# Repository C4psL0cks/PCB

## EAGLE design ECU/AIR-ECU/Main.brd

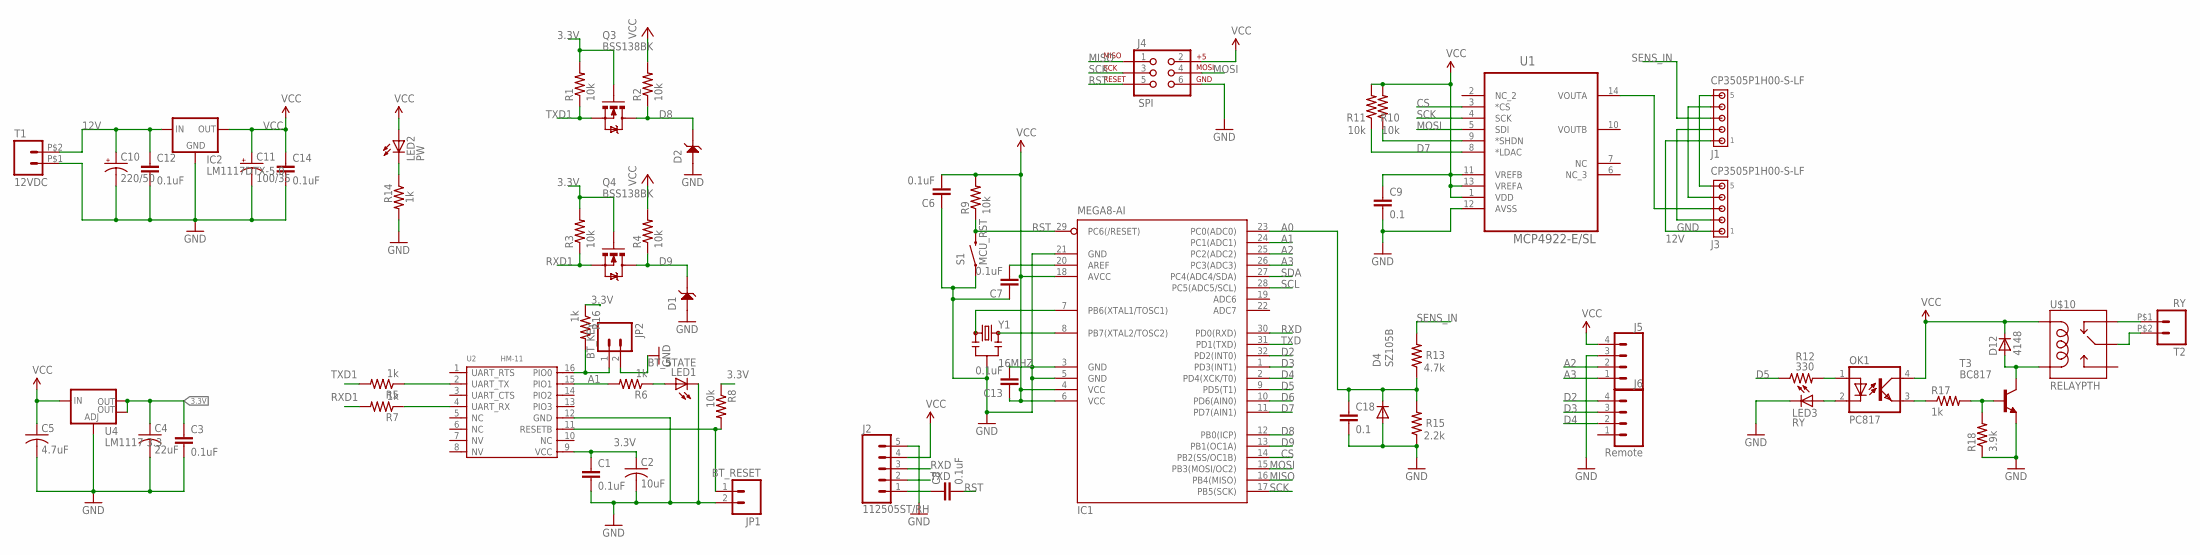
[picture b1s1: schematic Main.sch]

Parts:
C1, C3, C6, C7, C8, C12, C13, C14: 0.1uF; 0805
C2: 10uF; C1206
C4: 22uF; C1206
C5: 4.7uF; C1206
C9, C18: 0.1; 0805
C10: 220/50; 153CLV-1010
C11: 100/35; 153CLV-0605
D1, D2: SMF5.0A; SOD123-2.7X1.6
D4: SZ105B; DO-214AC
D12: 4148; SOD80
IC1: MEGA8-AI; TQFP32-08
IC2: LM1117DTX-5.0; TO252
J1, J3: CP3505P1H00-S-LF; 1445055-5
J2: 112505ST/RH; JST-5-PTH
J4: SPI; 2X3
J5: CONN_04JST-PTH; JST-4-PTH
J6: Remote; JST-4-PTH
JP1: BT_RESET; 1X02
JP2: BT_KEY; 1X02
LED1: BT_STATE; LED3MM
LED2: PW; LED3MM
LED3: RY; LED3MM
OK1: PC817; DIL4-SMD
Q3, Q4: BSS138BK; SOT23-3
R1, R2, R3, R4, R8, R9, R10, R11: 10k; 0805
R5, R6, R7, R14, R16, R17: 1k; 0805
R12: 330; 0805
R13: 4.7k; 0805
R15: 2.2k; 0805
R18: 3.9k; 0805
S1: MCU_RST; TACTILE-SWITCH-1101NE
T1: 12VDC; ED350V-02P
T2: RY; ED350V-02P
T3: BC817; SOT23-BEC
U1: MCP4922-E/SL; SOIC127P600X175-14N
U2: HM-11; 16P-18.5X13.5X0.8
U4: LM1117 3.3; SOT223
U$10: RELAYPTH; SRD-05VDC-SL-C
Y1: 16MHZ; RESONATOR-SMD

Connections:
3.3V: C1.1, C2.1, C3.1, C4.1, Q3.1 (G), Q4.1 (G), R1.2, R3.2, R8.1, R16.1, U2.9 (VCC), U4.2 (OUT), U4.4 (OUT)
12V: C10.+, C12.1, IC2.2 (IN), J1.1, J3.1, T1.P$2 (2)
A0: C18.1, D4.C, IC1.23 (PC0(ADC0)), R13.1, R15.2
A1: IC1.24 (PC1(ADC1)), R6.2, U2.15 (PIO1)
A2: IC1.25 (PC2(ADC2)), J5.2
A3: IC1.26 (PC3(ADC3)), J5.1
CS: IC1.14 (PB2(SS/OC1B)), U1.3 (*CS)
D2: IC1.32 (PD2(INT0)), J6.4
D3: IC1.1 (PD3(INT1)), J6.3
D4: IC1.2 (PD4(XCK/T0)), J6.2
D5: IC1.9 (PD5(T1)), R12.1
D6: IC1.10 (PD6(AIN0))
D7: IC1.11 (PD7(AIN1)), R11.1, U1.8 (*LDAC)
D8: D2.2, IC1.12 (PB0(ICP)), Q3.3 (D), R2.1
D9: D1.2, IC1.13 (PB1(OC1A)), Q4.3 (D), R4.1
GND: C1.2, C2.2, C3.2, C4.2, C5.2, C6.1, C7.1, C9.2, C10.-, C11.-, C12.2, C13.2, C14.2, C18.2, D1.1, D2.1, D4.A, IC1.3 (GND), IC1.5 (GND), IC1.21 (GND), IC2.1 (GND), J1.2, J2.5, J3.2, J4.6, J5.3, JP1.2, JP2.2, LED1.K (C), LED3.K (C), R14.2, R15.1, R18.1, S1.1, T1.P$1 (1), T3.E, U1.12 (AVSS), U2.12 (GND), U4.1 (ADJ), Y1.2
MISO: IC1.16 (PB4(MISO)), J4.1
MOSI: IC1.15 (PB3(MOSI/OC2)), J4.4, U1.5 (SDI)
unnamed: LED1.A, R6.1
unnamed: JP2.1, R16.2, U2.16 (PIO0)
unnamed: R5.1, U2.2 (UART_TX)
unnamed: JP1.1, R8.2, U2.11 (RESETB)
unnamed: IC1.8 (PB7(XTAL2/TOSC2)), Y1.3
unnamed: R7.1, U2.4 (UART_RX)
unnamed: IC1.7 (PB6(XTAL1/TOSC1)), Y1.1
unnamed: C7.2, IC1.20 (AREF)
unnamed: C8.1, J2.1
unnamed: LED2.K (C), R14.1
unnamed: J3.3, U1.14 (VOUTA)
unnamed: J1.5, J3.5
unnamed: J1.4, J3.4
unnamed: R10.1, U1.9 (*SHDN)
unnamed: OK1.3 (EMIT), R17.1
unnamed: R17.2, R18.2, T3.B
unnamed: D12.2 (A), T3.C, U$10.COIL0
unnamed: OK1.1 (A), R12.2
unnamed: T2.P$1 (1), U$10.SWCLOSED (SWCLOSE)
unnamed: T2.P$2 (2), U$10.SWCOMMON
unnamed: LED3.A, OK1.2 (C)
RST: C8.2, IC1.29 (PC6(/RESET)), J4.5, R9.1, S1.2
RXD: IC1.30 (PD0(RXD)), J2.3
RXD1: Q4.2 (S), R3.1, R7.2
SCK: IC1.17 (PB5(SCK)), J4.3, U1.4 (SCK)
SCL: IC1.28 (PC5(ADC5/SCL))
SDA: IC1.27 (PC4(ADC4/SDA))
SENS_IN: J1.3, R13.2
TXD: IC1.31 (PD1(TXD)), J2.2
TXD1: Q3.2 (S), R1.1, R5.2
VCC: C5.1, C6.2, C9.1, C11.+, C13.1, C14.1, D12.1 (C), IC1.4 (VCC), IC1.6 (VCC), IC1.18 (AVCC), IC2.TAB (OUT), J2.4, J4.2, J5.4, LED2.A, OK1.4 (COL), R2.2, R4.2, R9.2, R10.2, R11.2, U1.1 (VDD), U1.11 (VREFB), U1.13 (VREFA), U4.3 (IN), U$10.COIL1

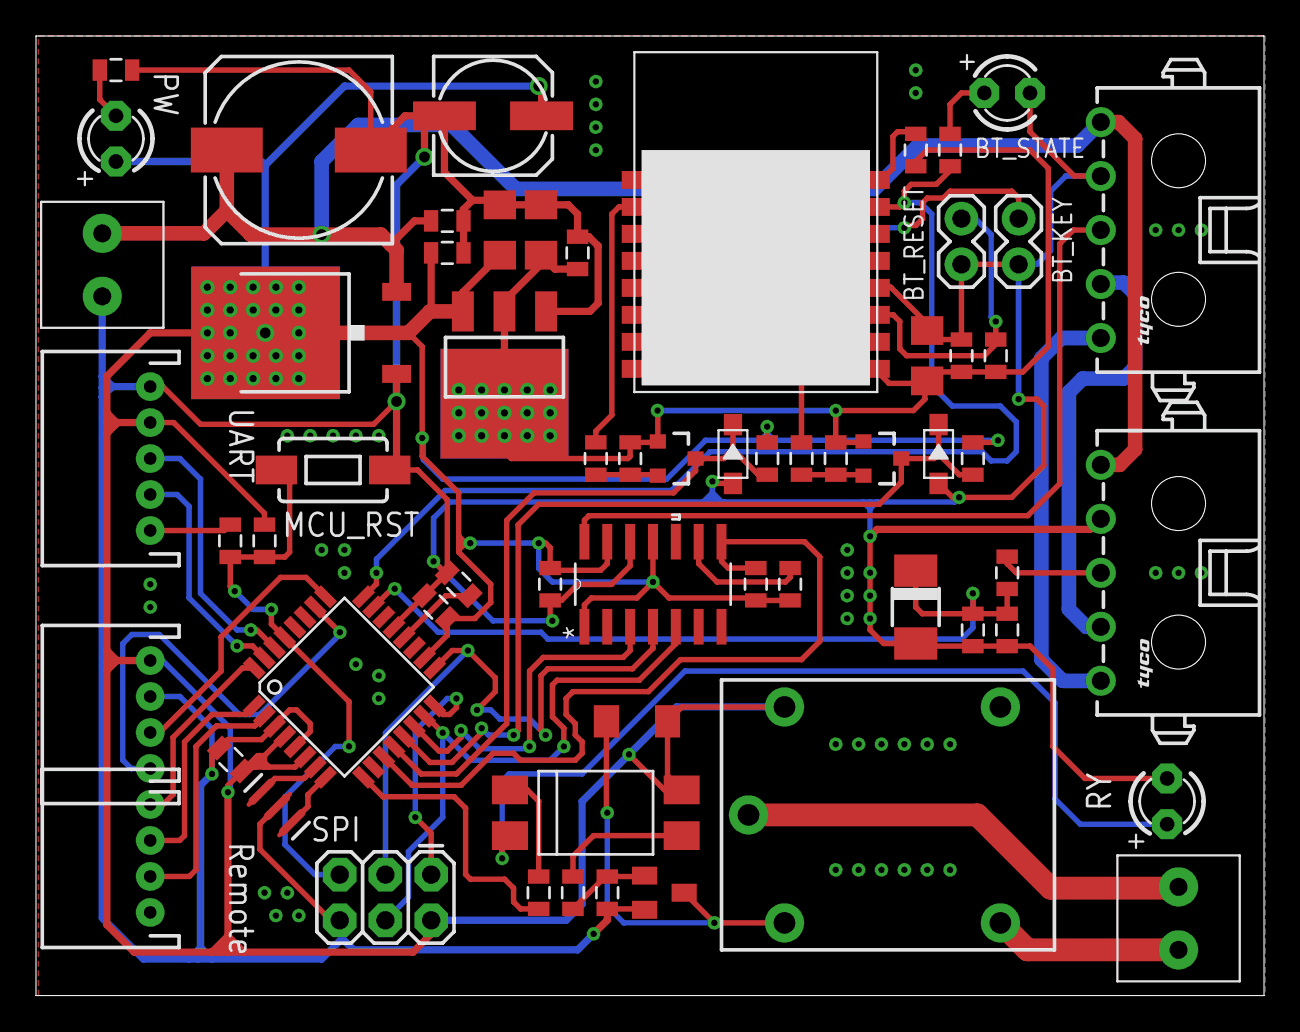
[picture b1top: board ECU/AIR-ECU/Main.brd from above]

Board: 2 copper layers, 68.2 x 53.3 mm, 62 parts (0 on the bottom side), 46 nets.

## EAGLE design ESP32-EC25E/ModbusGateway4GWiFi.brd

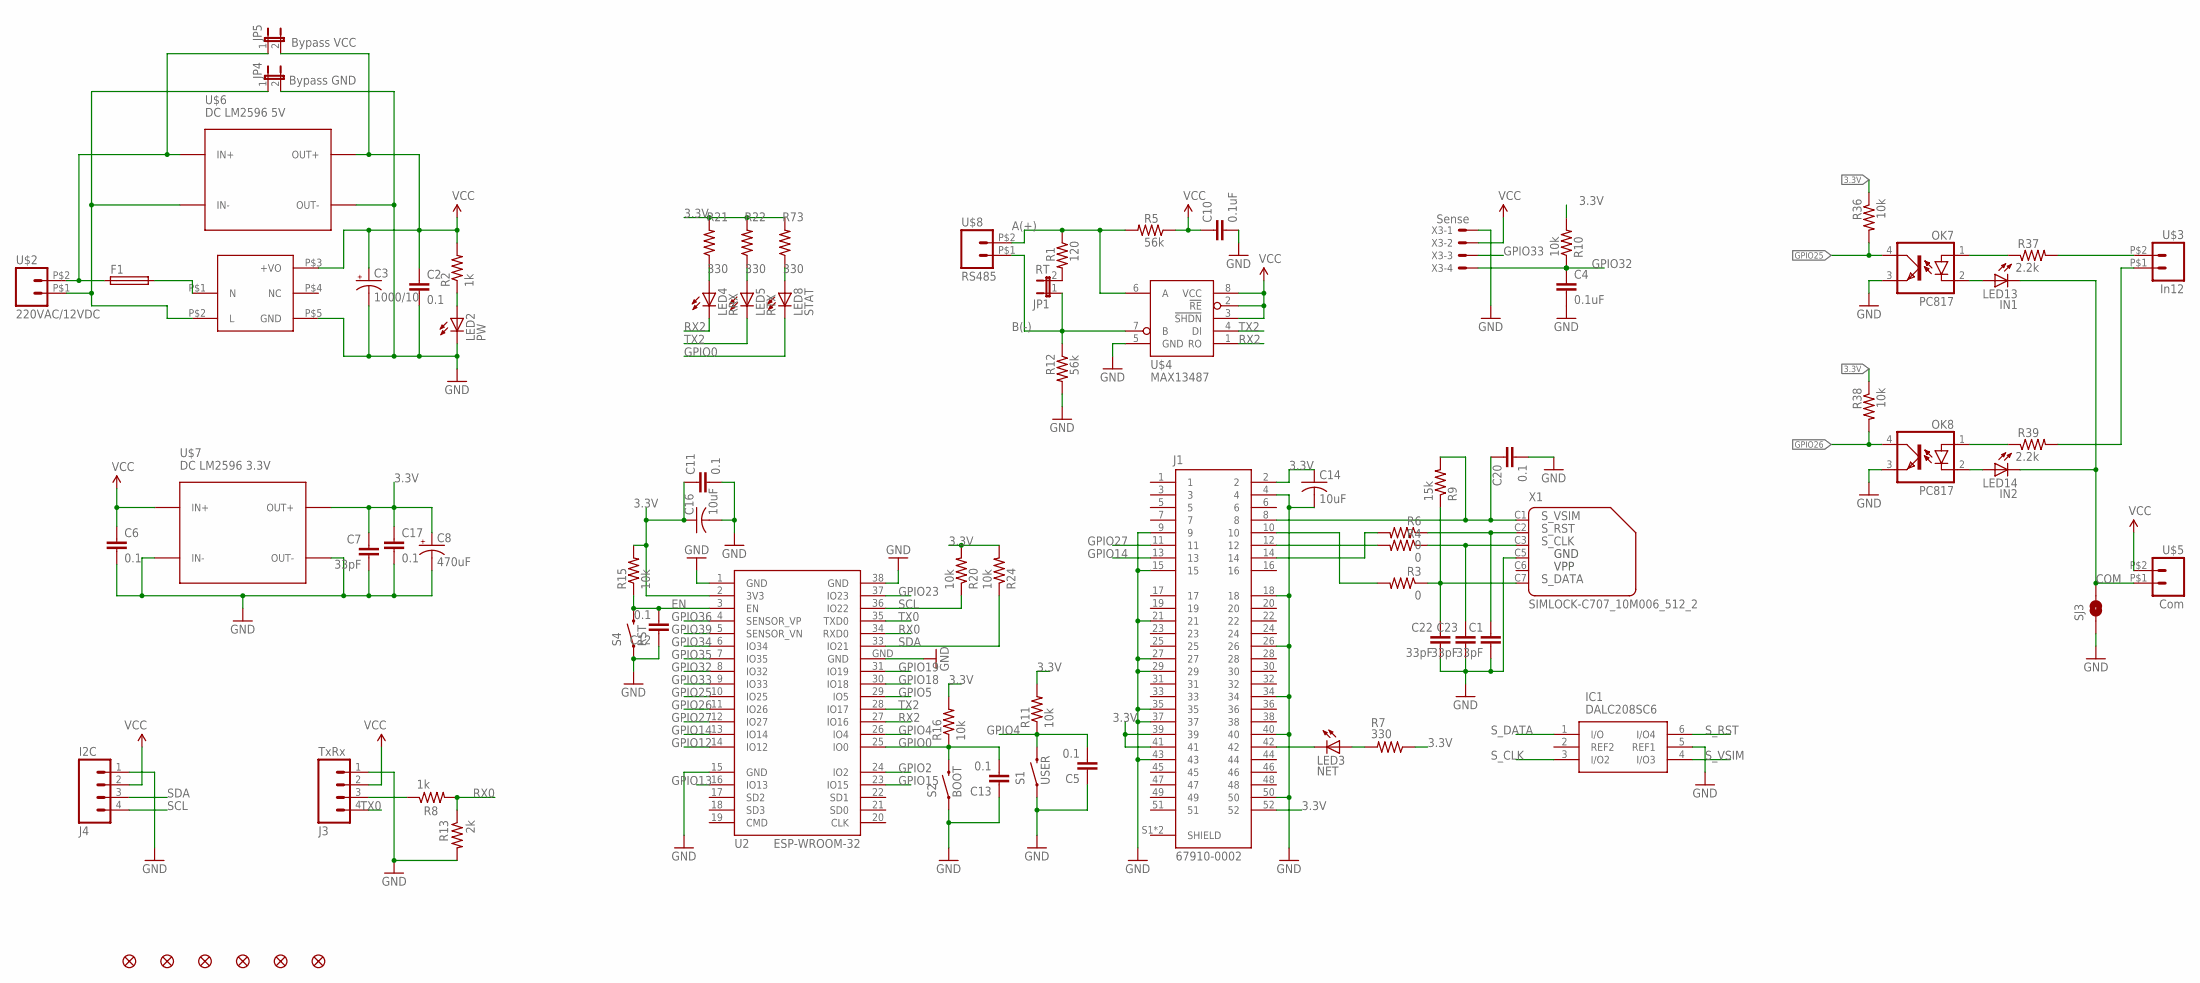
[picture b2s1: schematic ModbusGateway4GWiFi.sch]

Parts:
C1, C7, C22, C23: 33pF; 0805
C2, C5, C6, C11, C12, C13, C17, C20: 0.1; 0805
C3: 1000/10; 140CLH-1010
C4, C10: 0.1uF; 0805
C8: 470uF; 175TMP-0810
C14, C16: 10uF; C1206
F1: SH22,5A
IC1: DALC208SC6; SOT95P280X145-6N
J1: 67910-0002; MOLEX_67910-0002
J3: TxRx; MOLEX-1X4
J4: I2C; MOLEX-1X4
JP1: RT; 1X02
JP4: Bypass GND; SJ_2S-NO
JP5: Bypass VCC; SJ_2S-NO
JP8, JP9, JP10, JP11, JP12, JP16: FIDUCIAL1X2; FIDUCIAL-1X2
LED2: PW; CHIP-LED0805
LED3: NET; CHIP-LED0805
LED4: RRX; CHIP-LED0805
LED5: RTX; CHIP-LED0805
LED8: STAT; CHIP-LED0805
LED13: IN1; CHIP-LED0805
LED14: IN2; CHIP-LED0805
OK7, OK8: PC817; DIL4-SMD
R1: 120; 0805
R2, R8: 1k; 0805
R3, R4, R6: 0; 0805
R5, R12: 56k; 0805
R7, R21, R22, R73: 330; 0805
R9: 15k; 0805
R10, R11, R15, R16, R20, R24, R36, R38: 10k; 0805
R13: 2k; 0805
R37, R39: 2.2k; 0805
S1: USER; TACTILE-SWITCH-1101NE
S2: BOOT; TACTILE-SWITCH-1101NE
S4: RST; TACTILE-SWITCH-1101NE
SJ3: JUMP COM to GND; SJ_2S-NO
U2: ESP-WROOM-32
U$1: HIECUBE
U$2: 220VAC/12VDC; 5EHDRC-2P
U$3: In12; 5EHDRC-2P
U$4: MAX13487; SOIC8-1.27-5X4MM
U$5: Com; 5EHDRC-2P
U$6: DC LM2596 5V; DC-DC-STEP-DOWN-LM2596
U$7: DC LM2596 3.3V; DC-DC-STEP-DOWN-LM2596
U$8: RS485; 5EHDRC-2P
X1: SIMLOCK-C707_10M006_512_2; C707_10M006_512_2
X3: Sense; JST-XH-04-PACKAGE-LONG-PAD

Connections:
3.3V: C7.1, C8.+, C11.1, C14.1, C16.1, C17.1, J1.2, J1.39, J1.41, J1.52, R7.1, R10.2, R11.2, R15.2, R16.2, R20.2, R21.2, R22.2, R24.2, R36.1, R38.1, R73.2, U2.2 (3V3), U$7.OUT+
A(+): R1.1, R5.2, U$4.6 (A), U$8.P$2 (2)
B(-): JP1.1, R12.1, U$4.7 (B), U$8.P$1 (1)
COM: LED13.C, LED14.C, SJ3.2, U$5.P$1 (1)
EN: C12.2, R15.1, S4.2, U2.3 (EN)
GND: C1.2, C2.2, C3.-, C4.2, C5.1, C6.2, C7.2, C8.-, C10.2, C11.2, C12.1, C13.1, C14.2, C16.2, C17.2, C20.2, C22.2, C23.2, IC1.5 (REF1), J1.4, J1.9, J1.15, J1.18, J1.21, J1.26, J1.27, J1.29, J1.34, J1.35, J1.37, J1.40, J1.43, J1.50, J3.1, J4.1, JP4.2, LED2.C, OK7.3 (EMIT), OK8.3 (EMIT), R12.2, R13.2, S1.1, S2.1, S4.1, SJ3.1, U2.1 (GND), U2.15 (GND), U2.38 (GND), U2.GND, U$1.P$5 (GND), U$4.5 (GND), U$6.OUT-, U$7.IN-, U$7.OUT-, X1.C5 (4), X3.1
GPIO0: C13.2, LED8.C, R16.1, S2.2, U2.25 (IO0)
GPIO2: U2.24 (IO2)
GPIO4: C5.2, R11.1, S1.2, U2.26 (IO4)
GPIO5: U2.29 (IO5)
GPIO12: U2.14 (IO12)
GPIO13: U2.16 (IO13)
GPIO14: J1.13, U2.13 (IO14)
GPIO15: U2.23 (IO15)
GPIO18: U2.30 (IO18)
GPIO19: U2.31 (IO19)
GPIO23: U2.37 (IO23)
GPIO25: OK7.4 (COL), R36.2, U2.10 (IO25)
GPIO26: OK8.4 (COL), R38.2, U2.11 (IO26)
GPIO27: J1.11, U2.12 (IO27)
GPIO32: C4.1, R10.1, U2.8 (IO32), X3.4
GPIO33: U2.9 (IO33), X3.3
GPIO34: U2.6 (IO34)
GPIO35: U2.7 (IO35)
GPIO36: U2.4 (SENSOR_VP)
GPIO39: U2.5 (SENSOR_VN)
unnamed: JP1.2, R1.2
unnamed: J1.10, R3.2
unnamed: JP4.1, U$1.P$2 (L), U$2.P$1 (1), U$6.IN-
unnamed: LED2.A, R2.1
unnamed: J1.12, R4.2
unnamed: J3.3, R8.1
unnamed: J1.14, R6.2
unnamed: J1.42, LED3.C
unnamed: LED3.A, R7.2
unnamed: F1.2, U$1.P$1 (N)
unnamed: LED4.A, R21.1
unnamed: LED5.A, R22.1
unnamed: LED8.A, R73.1
unnamed: OK7.1 (A), R37.1
unnamed: LED13.A, OK7.2 (C)
unnamed: OK8.1 (A), R39.1
unnamed: LED14.A, OK8.2 (C)
unnamed: R37.2, U$3.P$2 (2)
unnamed: R39.2, U$3.P$1 (1)
RX0: R8.2, R13.1, U2.34 (RXD0)
RX2: LED4.C, U2.27 (IO16), U$4.1 (RO)
SCL: J4.4, R20.1, U2.36 (IO22)
SDA: J4.3, R24.1, U2.33 (IO21)
S_CLK: C23.1, IC1.3 (I/O2), R4.1, X1.C3 (3)
S_DATA: C22.1, IC1.1 (I/O), R3.1, R9.1, X1.C7 (6)
S_RST: C1.1, IC1.6 (I/O4), R6.1, X1.C2 (2)
S_VSIM: C20.1, IC1.4 (I/O3), J1.8, R9.2, X1.C1 (1)
TX0: J3.4, U2.35 (TXD0)
TX2: LED5.C, U2.28 (IO17), U$4.4 (DI)
VCC: C2.1, C3.+, C6.1, C10.1, J3.2, J4.2, JP5.2, R2.2, R5.1, U$1.P$3 (+VO), U$4.2 (!RE), U$4.3 (!SHDN), U$4.8 (VCC), U$5.P$2 (2), U$6.OUT+, U$7.IN+, X3.2
VS: F1.1, JP5.1, U$2.P$2 (2), U$6.IN+

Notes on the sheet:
GND
VPP

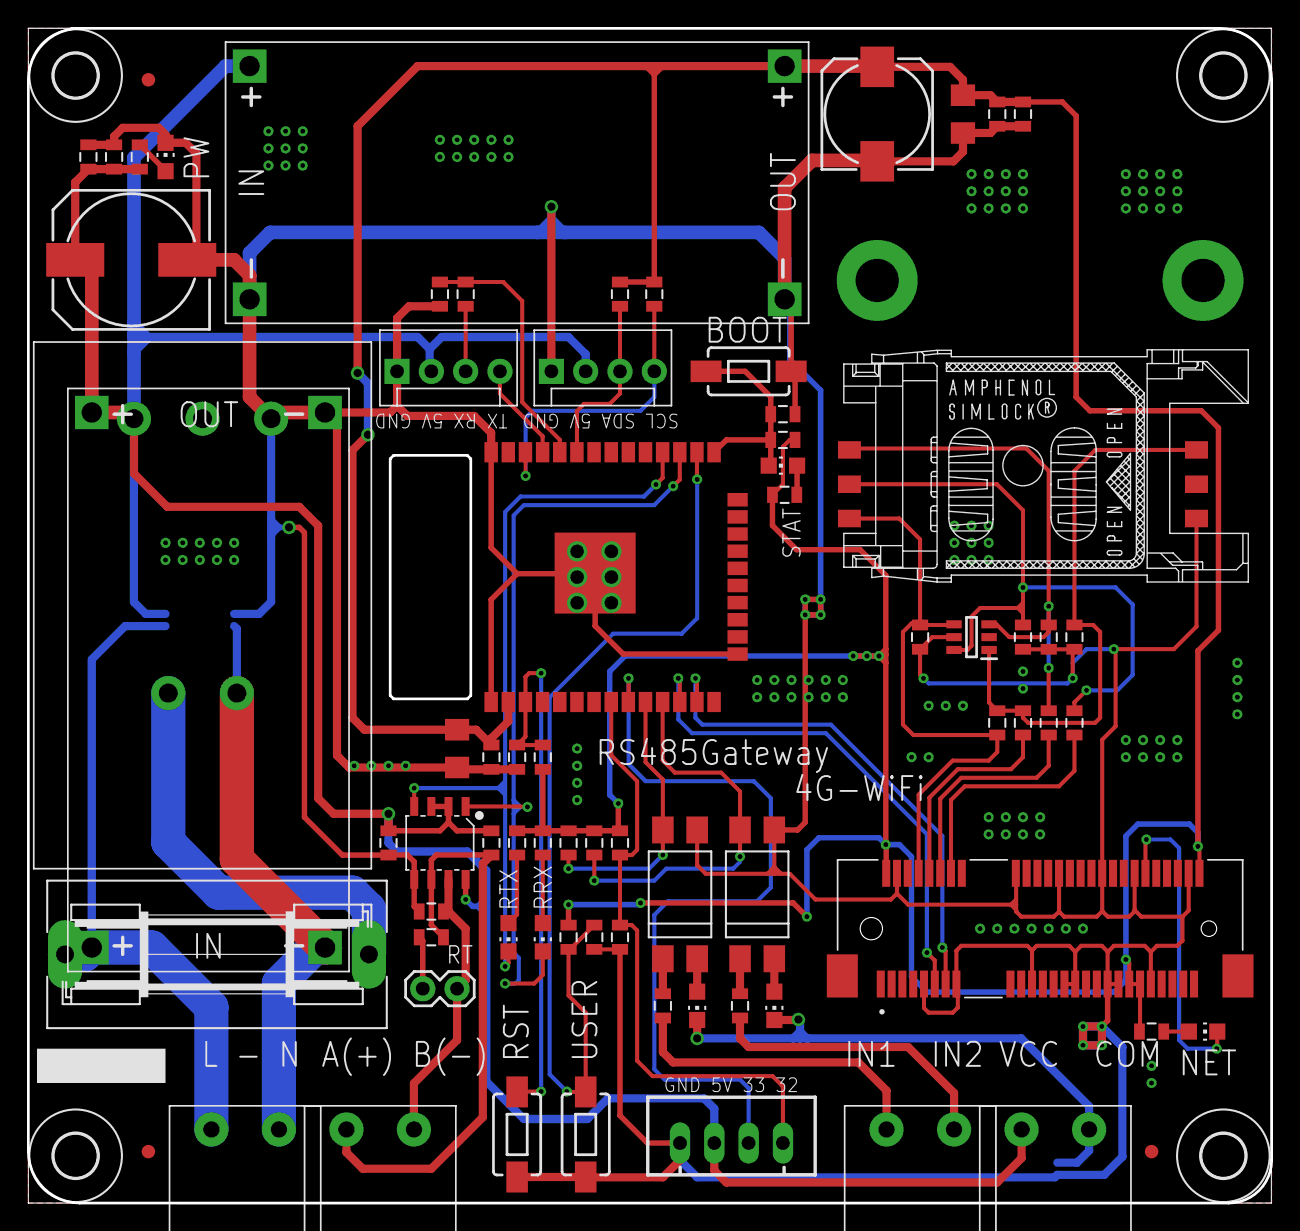
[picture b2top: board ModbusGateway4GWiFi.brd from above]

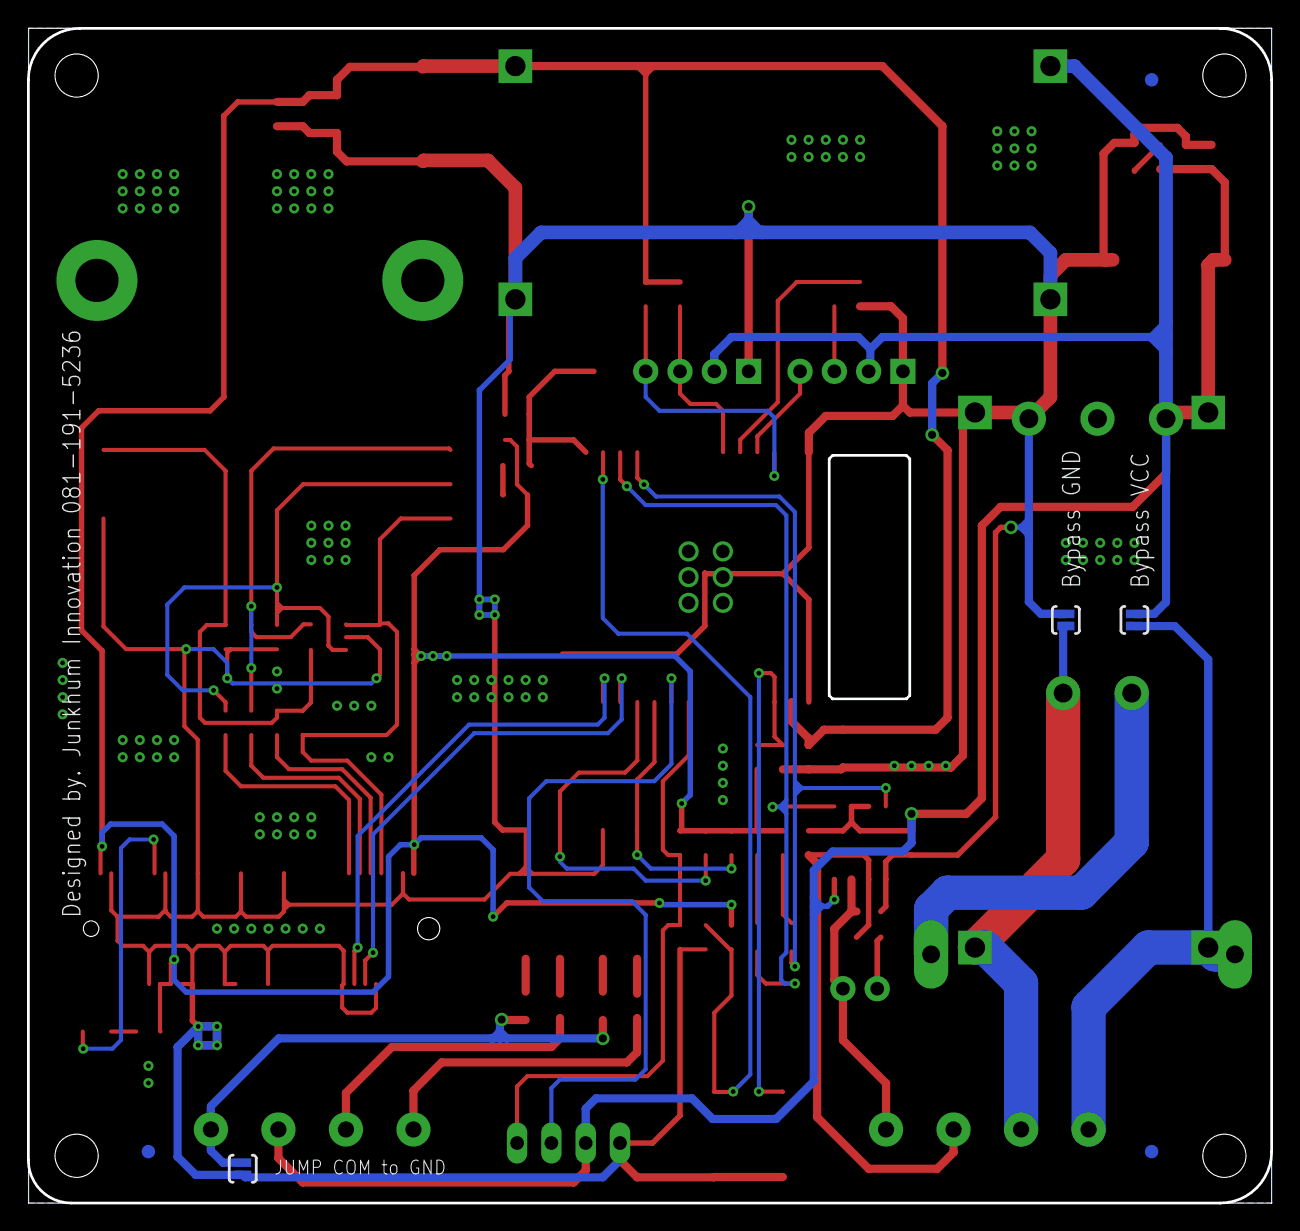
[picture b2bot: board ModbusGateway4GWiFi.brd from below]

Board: 2 copper layers, 92.1 x 87.0 mm, 84 parts (6 on the bottom side), 45 nets.

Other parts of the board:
U$15, U$16, U$17, U$18: 3,2

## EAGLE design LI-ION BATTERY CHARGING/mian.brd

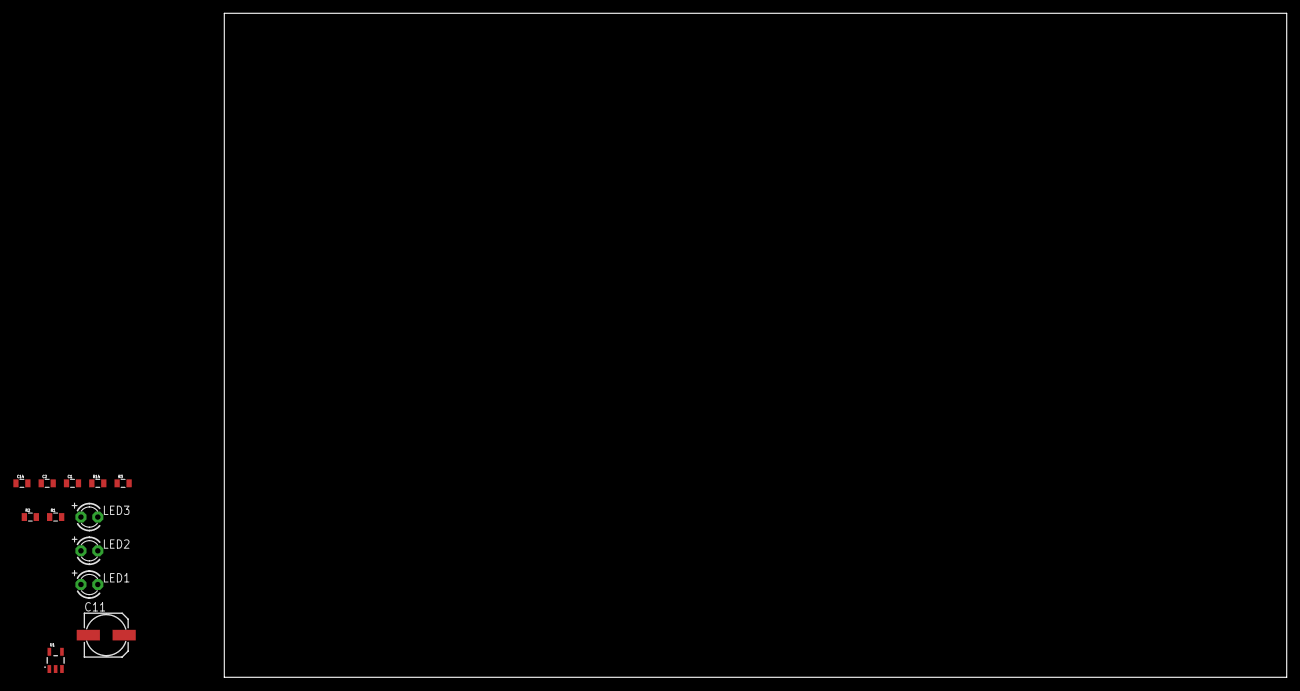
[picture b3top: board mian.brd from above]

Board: 2 copper layers, 160.0 x 100.0 mm, 12 parts (0 on the bottom side), 10 nets, no tracks yet.

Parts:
C1, C2: 10u; 0805
C11: 100/35; 153CLV-0605
C14: 0.1uF; 0805
LED1, LED2, LED3: PW; LED3MM
R1, R2: 470; 0805
R3: 2k2; 0805
R14: 1k; 0805
U1: MCP73831; SOT23-5

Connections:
GND: C1.2, C2.2, R1.2, R3.2, R14.2
unnamed: LED1.K, LED3.A, U1.1
unnamed: LED3.K, R1.1
unnamed: LED1.A, R2.2
unnamed: R3.1, U1.5
unnamed: C1.1, U1.3
unnamed: C2.1, R2.1, U1.4
unnamed: C11.-, C14.2
unnamed: LED2.K, R14.1
VCC: C11.+, C14.1, LED2.A

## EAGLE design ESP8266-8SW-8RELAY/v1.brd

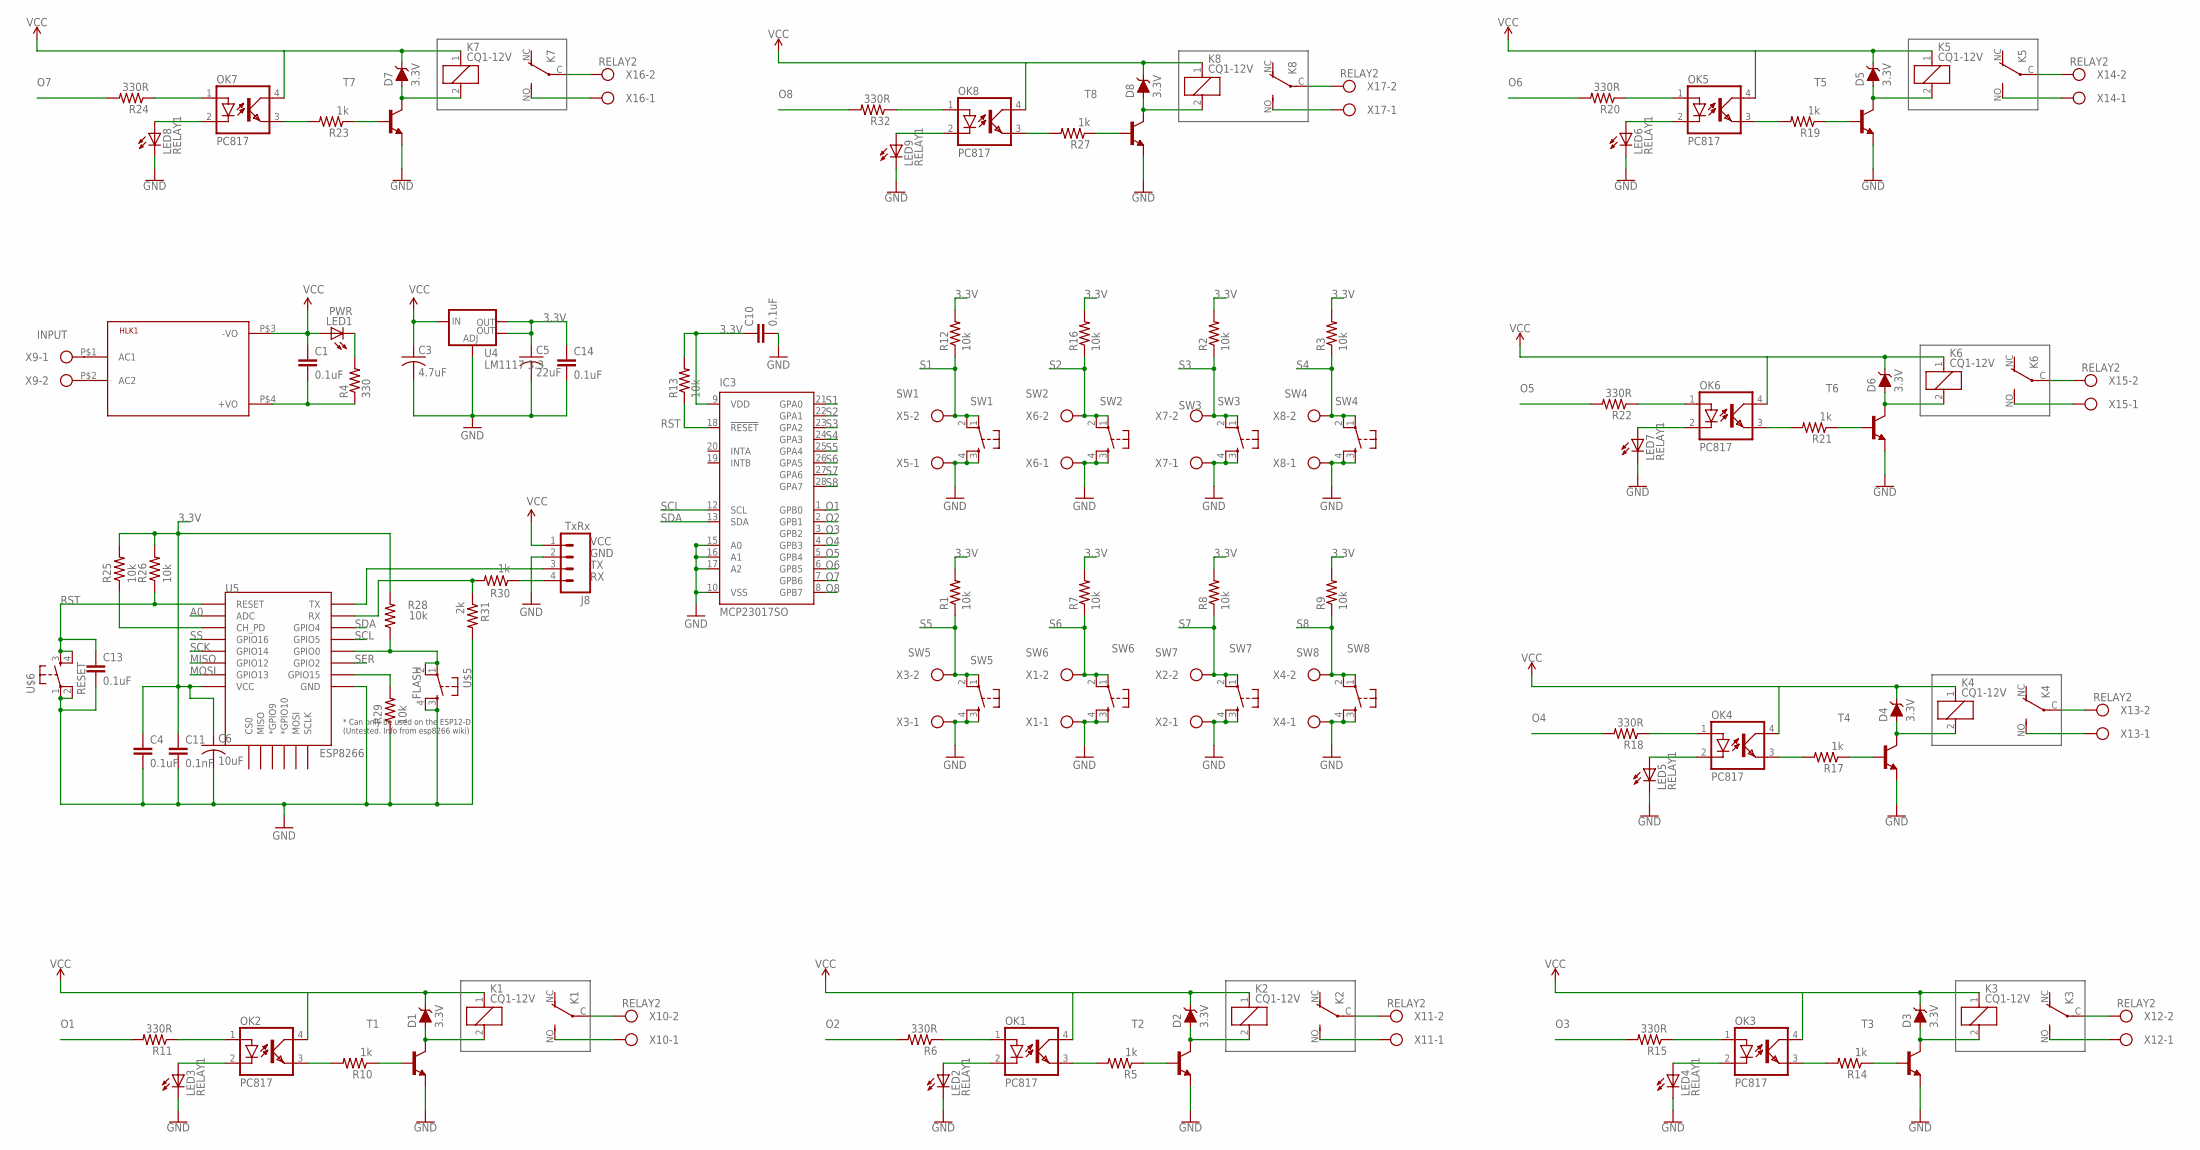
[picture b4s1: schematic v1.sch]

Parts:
C1, C4, C10, C13, C14: 0.1uF; 0805
C3: 4.7uF; C1206
C5: 22uF; C1206
C6: 10uF; C1206
C11: 0.1nF; 0805
D1, D2, D3, D4, D5, D6, D7, D8: 3.3V; SOD-323
HLK1: HLK-PM013W; HLK-PM01
IC3: MCP23017SO; SO28W
J8: TxRx; MOLEX-1X4
K1, K2, K3, K4, K5, K6, K7, K8: CQ1-12V; CQ1
LED1: PWR; CHIP-LED0805
LED2, LED3, LED4, LED5, LED6, LED7, LED8, LED9: RELAY1; CHIP-LED0805
OK1, OK2, OK3, OK4, OK5, OK6, OK7, OK8: PC817; DIL04
R1, R2, R3, R7, R8, R9, R12, R13, R16, R25, R26, R28, R29: 10k; 0805
R4: 330; 0805
R5, R10, R14, R17, R19, R21, R23, R27, R30: 1k; 0805
R6, R11, R15, R18, R20, R22, R24, R32: 330R; 0805
R31: 2k; 0805
T1, T2, T3, T4, T5, T6, T7, T8: -NPN-SOT23-BEC; SOT23-BEC
U4: LM1117 3.3; SOT223
U5: ESP8266; ESP12E-SMD
U$1: SW1; TAC-SWITCH-PTH
U$2: SW2; TAC-SWITCH-PTH
U$3: SW5; TAC-SWITCH-PTH
U$4: SW3; TAC-SWITCH-PTH
U$5: FLASH; TAC-SWITCH-PTH
U$6: RESET; TAC-SWITCH-PTH
U$7: SW4; TAC-SWITCH-PTH
U$8: SW6; TAC-SWITCH-PTH
U$9: SW7; TAC-SWITCH-PTH
U$10: SW8; TAC-SWITCH-PTH
X1: SW6; W237-102
X2: SW7; W237-102
X3: SW5; W237-102
X4: SW8; W237-102
X5: SW1; W237-102
X6: SW2; W237-102
X7: SW3; W237-102
X8: SW4; W237-102
X9: INPUT; W237-102
X10, X11, X12, X13, X14, X15, X16, X17: RELAY2; W237-102

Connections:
1: D2.A, K2.2, T2.C
2: D3.A, K3.2, T3.C
3: D4.A, K4.2, T4.C
3.3V: C4.1, C5.1, C6.1, C10.1, C11.1, C14.1, IC3.9 (VDD), R1.2, R2.2, R3.2, R7.2, R8.2, R9.2, R12.2, R13.2, R16.2, R25.2, R26.2, R28.2, U4.2 (OUT), U4.4 (OUT), U5.VCC
4: D5.A, K5.2, T5.C
5: D6.A, K6.2, T6.C
6: D7.A, K7.2, T7.C
7: D8.A, K8.2, T8.C
22: D1.A, K1.2, T1.C
A0: U5.ADC
GND: C3.2, C4.2, C5.2, C6.2, C10.2, C11.2, C13.2, C14.2, IC3.10 (VSS), IC3.15 (A0), IC3.16 (A1), IC3.17 (A2), J8.2, LED2.C, LED3.C, LED4.C, LED5.C, LED6.C, LED7.C, LED8.C, LED9.C, R29.1, R31.2, T1.E, T2.E, T3.E, T4.E, T5.E, T6.E, T7.E, T8.E, U4.1 (ADJ), U5.GND, U$1.3, U$1.4, U$2.3, U$2.4, U$3.3, U$3.4, U$4.3, U$4.4, U$5.3, U$5.4, U$6.1, U$6.2, U$7.3, U$7.4, U$8.3, U$8.4, U$9.3, U$9.4, U$10.3, U$10.4, X1.1, X2.1, X3.1, X4.1, X5.1, X6.1, X7.1, X8.1
INSS: OK2.1 (A), R11.1
INSS1: OK1.1 (A), R6.1
INSS2: OK3.1 (A), R15.1
INSS3: OK4.1 (A), R18.1
INSS4: OK5.1 (A), R20.1
INSS5: OK6.1 (A), R22.1
INSS6: OK7.1 (A), R24.1
INSS7: OK8.1 (A), R32.1
LEDS: LED3.A, OK2.2 (C)
LEDS1: LED2.A, OK1.2 (C)
LEDS2: LED4.A, OK3.2 (C)
LEDS3: LED5.A, OK4.2 (C)
LEDS4: LED6.A, OK5.2 (C)
LEDS5: LED7.A, OK6.2 (C)
LEDS6: LED8.A, OK7.2 (C)
LEDS7: LED9.A, OK8.2 (C)
MISO: U5.GPIO12
MOSI: U5.GPIO13
unnamed: C1.2, HLK1.P$4 (+VO), R4.1
unnamed: HLK1.P$1 (AC1), X9.1
unnamed: HLK1.P$2 (AC2), X9.2
unnamed: K1.NO (S), X10.1
unnamed: K1.C, X10.2
unnamed: R5.1, T2.B
unnamed: OK1.3 (EMIT), R5.2
unnamed: K2.NO (S), X11.1
unnamed: LED1.C, R4.2
unnamed: K2.C, X11.2
unnamed: R14.1, T3.B
unnamed: OK3.3 (EMIT), R14.2
unnamed: K3.NO (S), X12.1
unnamed: K3.C, X12.2
unnamed: R17.1, T4.B
unnamed: OK4.3 (EMIT), R17.2
unnamed: K4.NO (S), X13.1
unnamed: K4.C, X13.2
unnamed: R19.1, T5.B
unnamed: R10.1, T1.B
unnamed: OK5.3 (EMIT), R19.2
unnamed: OK2.3 (EMIT), R10.2
unnamed: K5.NO (S), X14.1
unnamed: K5.C, X14.2
unnamed: R21.1, T6.B
unnamed: R30.2, R31.1, U5.RXD0 (RX)
unnamed: OK6.3 (EMIT), R21.2
unnamed: K6.NO (S), X15.1
unnamed: K6.C, X15.2
unnamed: R23.1, T7.B
unnamed: OK7.3 (EMIT), R23.2
unnamed: K7.NO (S), X16.1
unnamed: K7.C, X16.2
unnamed: R27.1, T8.B
unnamed: OK8.3 (EMIT), R27.2
unnamed: R25.1, U5.CH_PD
unnamed: R28.1, U5.GPIO0, U$5.1, U$5.2
unnamed: R29.2, U5.GPIO15
unnamed: K8.NO (S), X17.1
unnamed: K8.C, X17.2
O1: IC3.1 (GPB0), R11.2
O2: IC3.2 (GPB1), R6.2
O3: IC3.3 (GPB2), R15.2
O4: IC3.4 (GPB3), R18.2
O5: IC3.5 (GPB4), R22.2
O6: IC3.6 (GPB5), R20.2
O7: IC3.7 (GPB6), R24.2
O8: IC3.8 (GPB7), R32.2
RST: C13.1, IC3.18 (!RESET), R13.1, R26.1, U5.RESET, U$6.3, U$6.4
RX: J8.4, R30.1
S1: IC3.21 (GPA0), R12.1, U$1.1, U$1.2, X5.2
S2: IC3.22 (GPA1), R16.1, U$2.1, U$2.2, X6.2
S3: IC3.23 (GPA2), R2.1, U$4.1, U$4.2, X7.2
S4: IC3.24 (GPA3), R3.1, U$7.1, U$7.2, X8.2
S5: IC3.25 (GPA4), R1.1, U$3.1, U$3.2, X3.2
S6: IC3.26 (GPA5), R7.1, U$8.1, U$8.2, X1.2
S7: IC3.27 (GPA6), R8.1, U$9.1, U$9.2, X2.2
S8: IC3.28 (GPA7), R9.1, U$10.1, U$10.2, X4.2
SCK: U5.GPIO14
SCL: IC3.12 (SCL), U5.GPIO5
SDA: IC3.13 (SDA), U5.GPIO4
SER: U5.GPIO2
SS: U5.GPIO16
TX: J8.3, U5.TXD0 (TX)
VCC: C1.1, C3.1, D1.C, D2.C, D3.C, D4.C, D5.C, D6.C, D7.C, D8.C, HLK1.P$3 (-VO), J8.1, K1.1, K2.1, K3.1, K4.1, K5.1, K6.1, K7.1, K8.1, LED1.A, OK1.4 (COL), OK2.4 (COL), OK3.4 (COL), OK4.4 (COL), OK5.4 (COL), OK6.4 (COL), OK7.4 (COL), OK8.4 (COL), U4.3 (IN)

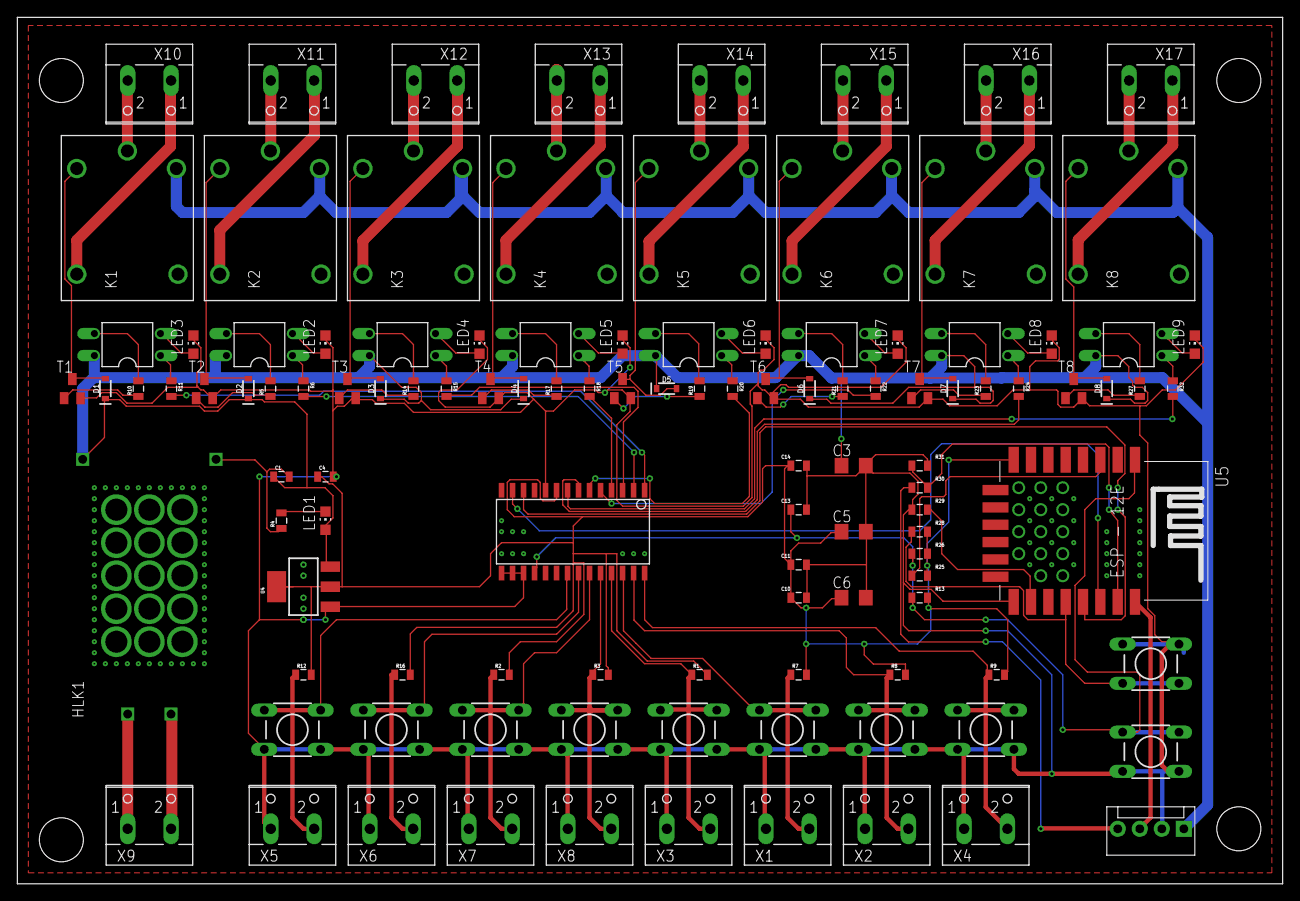
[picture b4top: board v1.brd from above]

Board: 2 copper layers, 146.0 x 100.0 mm, 114 parts (0 on the bottom side), 88 nets.

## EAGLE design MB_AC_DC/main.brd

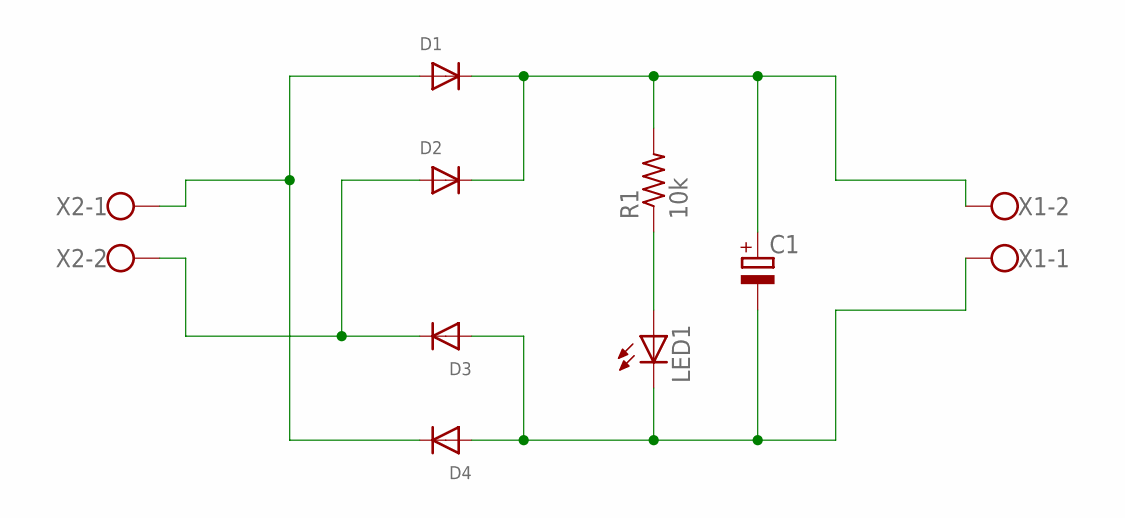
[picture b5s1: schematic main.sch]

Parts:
C1: C-POL_RADIAL-25MM-DIA; CAPPRD550W110D1250H2500B
D1, D2, D3, D4: DIODEDO-1N4148; DO-1N4148
LED1: LED5MM
R1: 10k; 0204/7
X1, X2: W237-102

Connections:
unnamed: D1.A, D4.C, X2.1
unnamed: D2.A, D3.C, X2.2
unnamed: C1.1 (+), D1.C, D2.C, R1.2, X1.2
unnamed: C1.2 (-), D3.A, D4.A, LED1.K (C), X1.1
unnamed: LED1.A, R1.1

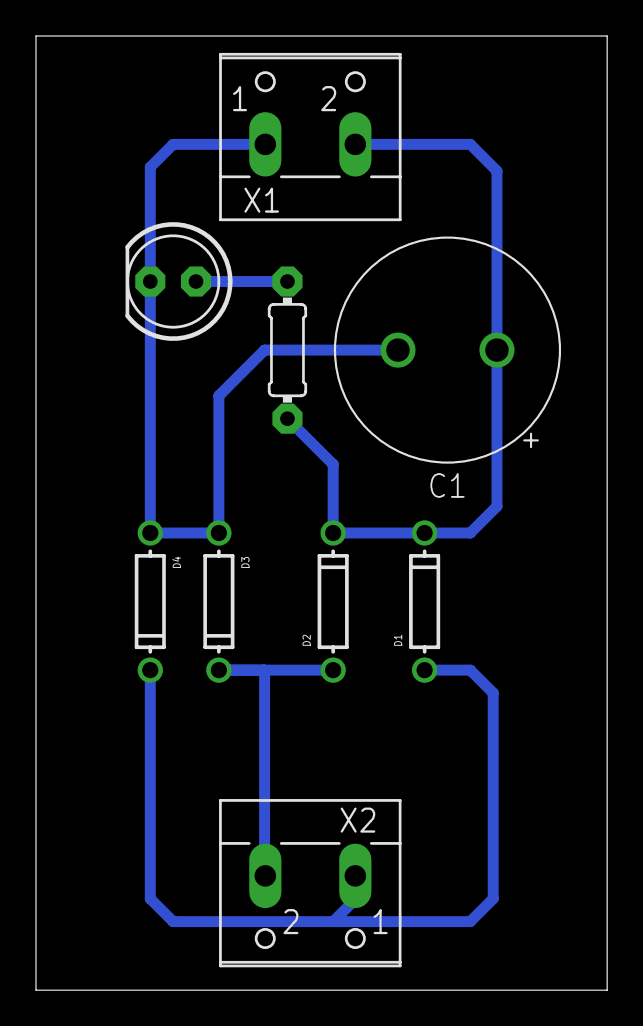
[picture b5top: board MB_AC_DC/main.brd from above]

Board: 2 copper layers, 31.7 x 53.0 mm, 9 parts (0 on the bottom side), 5 nets.

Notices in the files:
parts and their libraries:
SparkFun-Connectors: Licensing: Creative Commons ShareAlike 4.0 International - https://creativecommons.org/licenses/by-sa/4.0
SparkFun: Licensing: CC v3.0 Share-Alike You are welcome to use this library for commercial purposes.
esp32: Creative Commons Attribution-ShareAlike 4.0 International
